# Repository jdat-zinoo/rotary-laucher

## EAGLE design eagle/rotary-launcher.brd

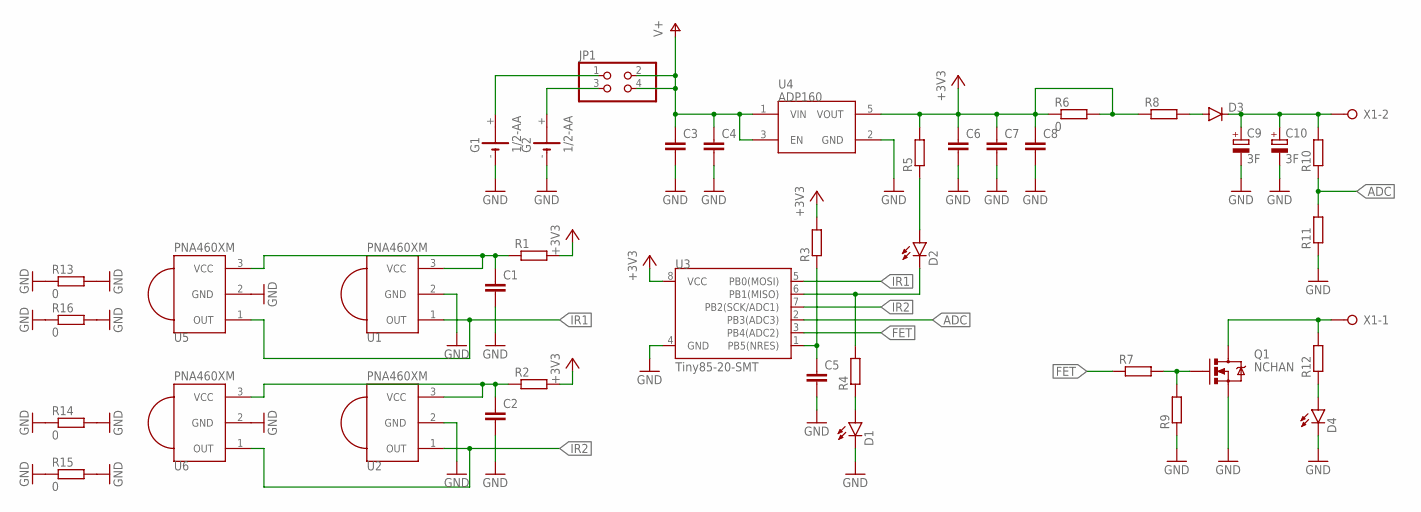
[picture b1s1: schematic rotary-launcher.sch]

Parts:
C1, C2, C3, C4, C5, C6, C7, C8: C-EUC0805; C0805
C9, C10: 3F; E3,5-8-HOR
D1, D2, D4: LED0603; LED-0603
D3: DIODESMB; SMB-DIODE
G1, G2: 1/2-AA; CRAA
JP1: PINHD-2X2; 2X02
Q1: NCHAN; SOT23-3
R1, R2, R3, R4, R5, R7, R9, R10, R11, R12: R-EU_R0603; R0603
R6, R13, R14, R15, R16: 0; R1206
R8: R-EU_R1206; R1206
U1, U2, U5, U6: PNA460XM
U3: Tiny85-20-SMT; SO08-EIAJ
U4: ADP160; SOT23-5
X1: W237-02P; W237-132

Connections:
+3V3: C6.1, C7.1, C8.1, R1.2, R2.2, R3.2, R5.2, R6.1, R6.2, R8.1, U3.8 (VCC), U4.5 (VOUT)
ADC: R10.1, R11.2, U3.2 (PB3(ADC3))
FET: R7.1, U3.3 (PB4(ADC2))
GND: C1.2, C2.2, C3.2, C4.2, C5.2, C6.2, C7.2, C8.2, C9.-, C10.-, D1.C, D4.C, G1.-, G2.-, Q1.2 (S), R9.1, R11.1, R13.1, R13.2, R14.1, R14.2, R15.1, R15.2, R16.1, R16.2, U1.2 (GND), U2.2 (GND), U3.4 (GND), U4.2 (GND), U5.2 (GND), U6.2 (GND)
IR1: U1.1 (OUT), U3.5 (PB0(MOSI)), U5.1 (OUT)
IR2: U2.1 (OUT), U3.7 (PB2(SCK/ADC1)), U6.1 (OUT)
unnamed: D3.A, R8.2
unnamed: C9.+, C10.+, D3.C, R10.2, X1.2
unnamed: G1.+, JP1.1
unnamed: G2.+, JP1.3
unnamed: C1.1, R1.1, U1.3 (VCC), U5.3 (VCC)
unnamed: Q1.1 (G), R7.2, R9.2
unnamed: C2.1, R2.1, U2.3 (VCC), U6.3 (VCC)
unnamed: C5.1, R3.1, U3.1 (PB5(NRES))
unnamed: Q1.3 (D), R12.2, X1.1
unnamed: D4.A, R12.1
unnamed: D2.C, R4.2, U3.6 (PB1(MISO))
unnamed: D2.A, R5.1
unnamed: D1.A, R4.1
V+: C3.1, C4.1, JP1.2, JP1.4, U4.1 (VIN), U4.3 (EN)

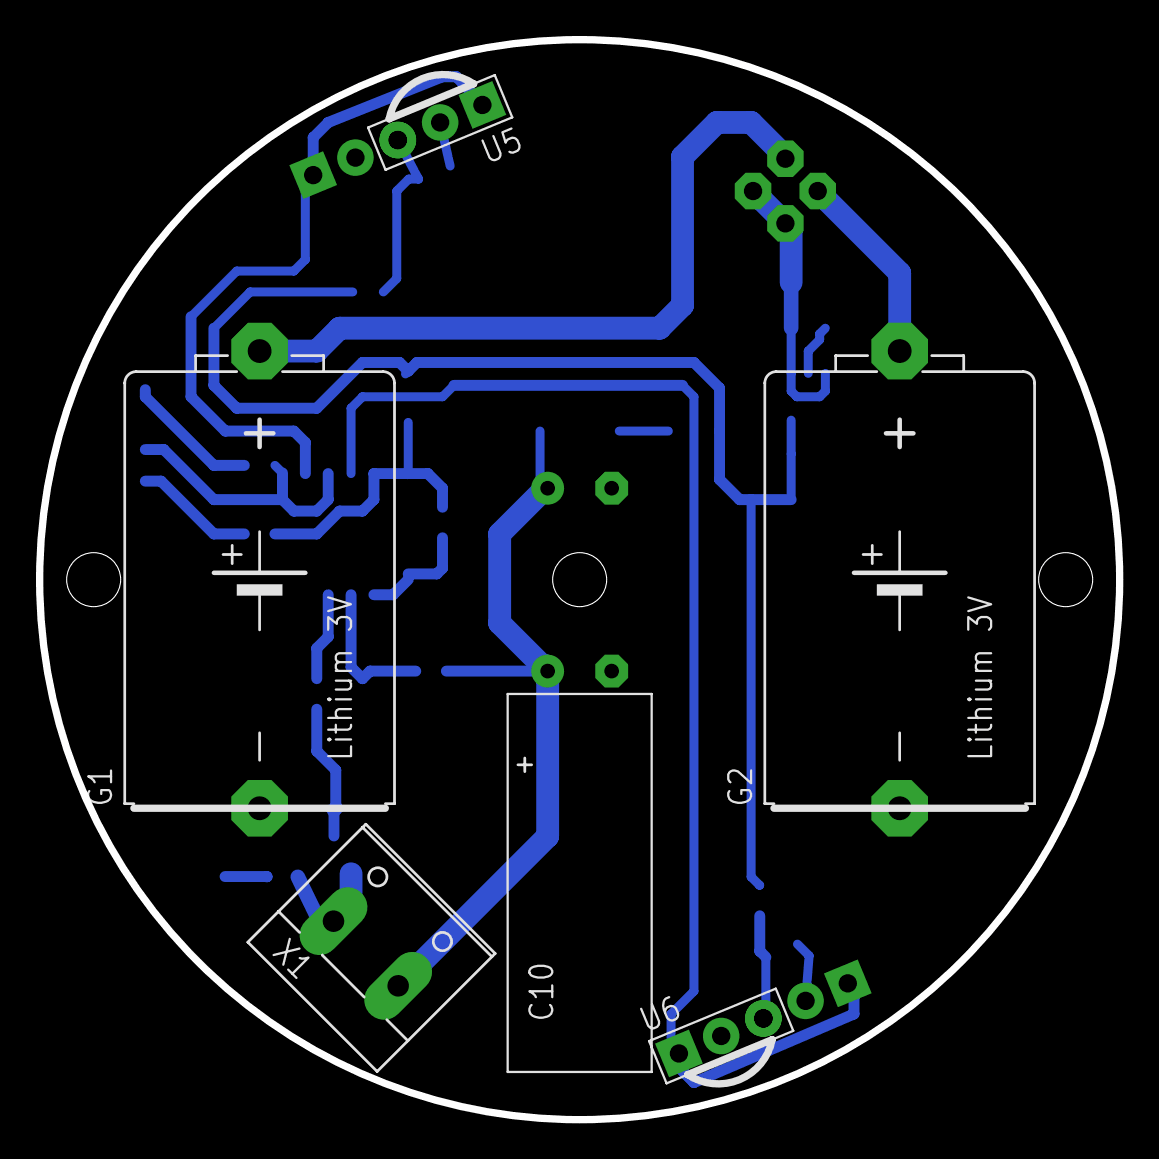
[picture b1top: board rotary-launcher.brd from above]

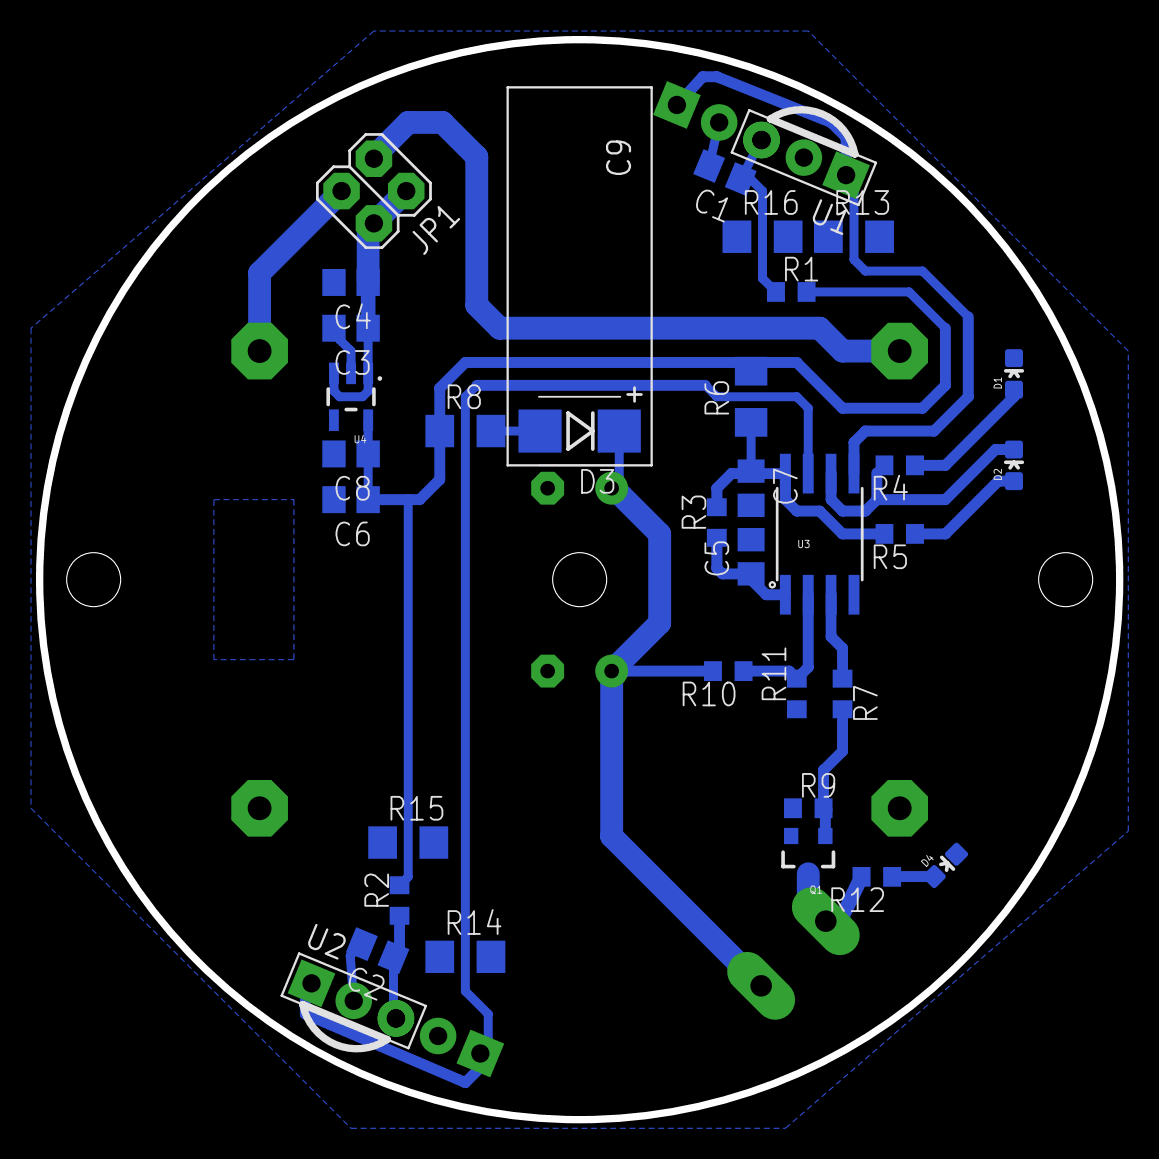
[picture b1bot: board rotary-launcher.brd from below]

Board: 2 copper layers, 60.0 x 60.0 mm, 41 parts (35 on the bottom side), 20 nets.

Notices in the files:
parts and their libraries:
SparkFun-DiscreteSemi: Licensing: Creative Commons ShareAlike 4.0 International - https://creativecommons.org/licenses/by-sa/4.0
